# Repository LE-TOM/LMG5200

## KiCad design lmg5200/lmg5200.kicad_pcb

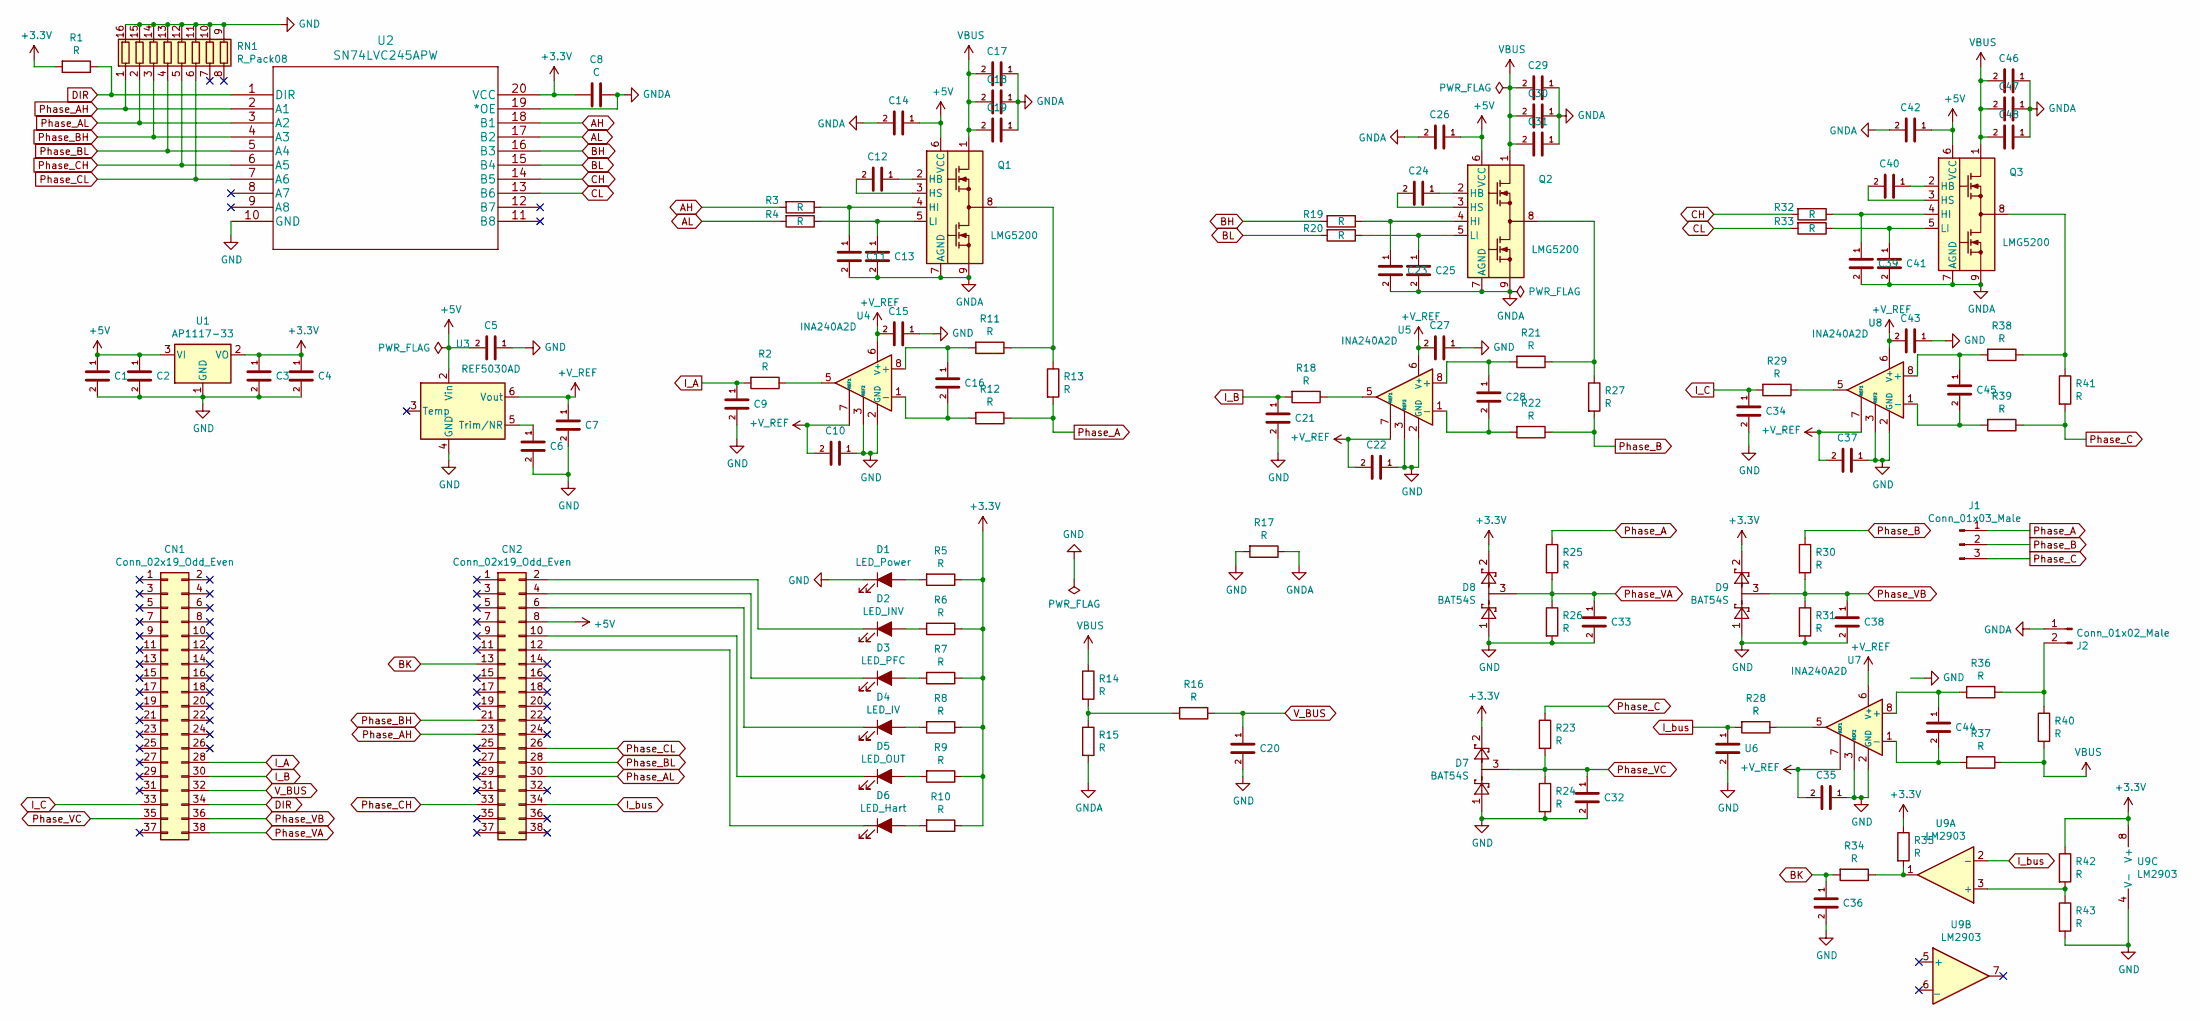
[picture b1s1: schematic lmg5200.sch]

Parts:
C1, C2, C3, C4, C5, C6, C7, C9, C10, C11, C12, C13, C14, C15, C16, C20, C21, C22, C23, C24, C25, C26, C27, C28, C32, C33, C34, C35, C36, C37, C38, C39, C40, C41, C42, C43, C44, C45: CAP; C_0805_2012Metric
C8: C; C_0805_2012Metric
C17, C18, C19, C29, C30, C31, C46, C47, C48: CAP; C_1206_3216Metric
CN1, CN2: Conn_02x19_Odd_Even; PinHeader_2x23_P2.54mm_Vertical
D1: LED_Power; LED_0805_2012Metric
D2: LED_INV; LED_0805_2012Metric
D3: LED_PFC; LED_0805_2012Metric
D4: LED_IV; LED_0805_2012Metric
D5: LED_OUT; LED_0805_2012Metric
D6: LED_Hart; LED_0805_2012Metric
D7, D8, D9: BAT54S; SOT-23
J1: Conn_01x03_Male; PhoenixContact_MSTB_2,5_3-GF_1x03_P5.00mm_Horizontal_Thread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
J2: Conn_01x02_Male; PhoenixContact_MSTB_2,5_2-GF_1x02_P5.00mm_Horizontal_Thread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
Q1, Q2, Q3: LMG5200; Texas_MOF0009A
R1, R2, R3, R4, R5, R6, R7, R8, R9, R10, R11, R12, R14, R15, R16, R17, R18, R19, R20, R21, R22, R23, R24, R25, R26, R28, R29, R30, R31, R32, R33, R34, R35, R36, R37, R38, R39, R42, R43: R; R_0805_2012Metric
R13, R27, R40, R41: R; R_2512_6332Metric
RN1: R_Pack08; R_Array_Convex_8x0602
U1: AP1117-33; SOT-223-3_TabPin2
U2: SN74LVC245APW; SOIC-20W_7.5x12.8mm_P1.27mm
U3: REF5030AD; SOIC-8_3.9x4.9mm_P1.27mm
U4, U5, U7, U8: INA240A2D; SOIC-8_3.9x4.9mm_P1.27mm
U6: CAP; C_0805_2012Metric
U9: LM2903; SOIC-8-N7_3.9x4.9mm_P1.27mm

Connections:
+5V: C1.1, C2.1, C5.2, C14.1, C26.1, C42.1, CN2.8, Q1.6 (VCC), Q2.6 (VCC), Q3.6 (VCC), U1.3 (VI), U3.2 (Vin)
AH: R3.2, U2.18 (B1)
AL: R4.2, U2.17 (B2)
BH: R19.2, U2.16 (B3)
BK: C36.1, CN2.13, R34.2
BL: R20.2, U2.15 (B4)
CH: R32.2, U2.14 (B5)
CL: R33.2, U2.13 (B6)
DIR: CN1.34, R1.1, U2.1 (DIR)
GND: C1.2, C2.2, C3.2, C4.2, C5.1, C6.2, C7.2, C9.2, C10.1, C15.1, C20.2, C21.2, C22.1, C27.1, C32.2, C33.2, C34.2, C35.1, C36.2, C37.1, C38.2, C43.1, D1.1 (K), D7.1, D8.1, D9.1, R17.2, R24.2, R26.2, R31.2, R43.2, RN1.9 (R8.2), RN1.10 (R7.2), RN1.11 (R6.2), RN1.12 (R5.2), RN1.13 (R4.2), RN1.14 (R3.2), RN1.15 (R2.2), RN1.16 (R1.2), U1.1 (GND), U2.10 (GND), U3.4 (GND), U4.2 (GND), U4.3 (REF2), U4.4 (GND), U5.2 (GND), U5.3 (REF2), U5.4 (GND), U6.2, U7.2 (GND), U7.3 (REF2), U7.4 (GND), U8.2 (GND), U8.3 (REF2), U8.4 (GND), U9.4 (V-)
GNDA: C8.1, C11.2, C13.2, C14.2, C17.1, C18.1, C19.1, C23.2, C25.2, C26.2, C29.1, C30.1, C31.1, C39.2, C41.2, C42.2, C46.1, C47.1, C48.1, J2.1, Q1.7 (AGND), Q1.9, Q2.7 (AGND), Q2.9, Q3.7 (AGND), Q3.9, R15.2, R17.1, U2.19 (*OE)
I_A: C9.1, CN1.28, R2.2
I_B: C21.1, CN1.30, R18.2
I_C: C34.1, CN1.33, R29.2
I_bus: CN2.34, R28.2, U6.1, U9.2 (-)
unnamed: C6.1, U3.5 (Trim/NR)
unnamed: C11.1, Q1.4 (HI), R3.1
unnamed: C12.1, Q1.2 (HB)
unnamed: C12.2, Q1.3 (HS)
unnamed: C13.1, Q1.5 (LI), R4.1
unnamed: C16.1, R11.2, U4.8 (+)
unnamed: C16.2, R12.2, U4.1 (-)
unnamed: C23.1, Q2.4 (HI), R19.1
unnamed: C24.1, Q2.2 (HB)
unnamed: C24.2, Q2.3 (HS)
unnamed: C25.1, Q2.5 (LI), R20.1
unnamed: C28.1, R21.2, U5.8 (+)
unnamed: C28.2, R22.2, U5.1 (-)
unnamed: C39.1, Q3.4 (HI), R32.1
unnamed: C40.1, Q3.2 (HB)
unnamed: C40.2, Q3.3 (HS)
unnamed: C41.1, Q3.5 (LI), R33.1
unnamed: C44.1, R36.2, U7.8 (+)
unnamed: C44.2, R37.2, U7.1 (-)
unnamed: C45.1, R38.2, U8.8 (+)
unnamed: C45.2, R39.2, U8.1 (-)
unnamed: CN2.2, D2.1 (K)
unnamed: CN2.4, D3.1 (K)
unnamed: CN2.6, D4.1 (K)
unnamed: CN2.10, D5.1 (K)
unnamed: CN2.12, D6.1 (K)
unnamed: D1.2 (A), R5.2
unnamed: D2.2 (A), R6.2
unnamed: D3.2 (A), R7.2
unnamed: D4.2 (A), R8.2
unnamed: D5.2 (A), R9.2
unnamed: D6.2 (A), R10.2
unnamed: J2.2, R36.1, R40.1
unnamed: Q1.8, R11.1, R13.1
unnamed: Q2.8, R21.1, R27.1
unnamed: Q3.8, R38.1, R41.1
unnamed: R2.1, U4.5
unnamed: R14.2, R15.1, R16.2
unnamed: R18.1, U5.5
unnamed: R28.1, U7.5
unnamed: R29.1, U8.5
unnamed: R34.1, R35.2, U9.1
unnamed: R42.2, R43.1, U9.3 (+)
Phase_A: J1.1, R12.1, R13.2, R25.1
Phase_AH: CN2.23, RN1.1 (R1.1), U2.2 (A1)
Phase_AL: CN2.30, RN1.2 (R2.1), U2.3 (A2)
Phase_B: J1.2, R22.1, R27.2, R30.1
Phase_BH: CN2.21, RN1.3 (R3.1), U2.4 (A3)
Phase_BL: CN2.28, RN1.4 (R4.1), U2.5 (A4)
Phase_C: J1.3, R23.1, R39.1, R41.2
Phase_CH: CN2.33, RN1.5 (R5.1), U2.6 (A5)
Phase_CL: CN2.26, RN1.6 (R6.1), U2.7 (A6)
Phase_VA: C33.1, CN1.38, D8.3, R25.2, R26.1
Phase_VB: C38.1, CN1.36, D9.3, R30.2, R31.1
Phase_VC: C32.1, CN1.35, D7.3, R23.2, R24.1
VBUS: C17.2, C18.2, C19.2, C29.2, C30.2, C31.2, C46.2, C47.2, C48.2, Q1.1, Q2.1, Q3.1, R14.1, R37.1, R40.2
V_BUS: C20.1, CN1.32, R16.1

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
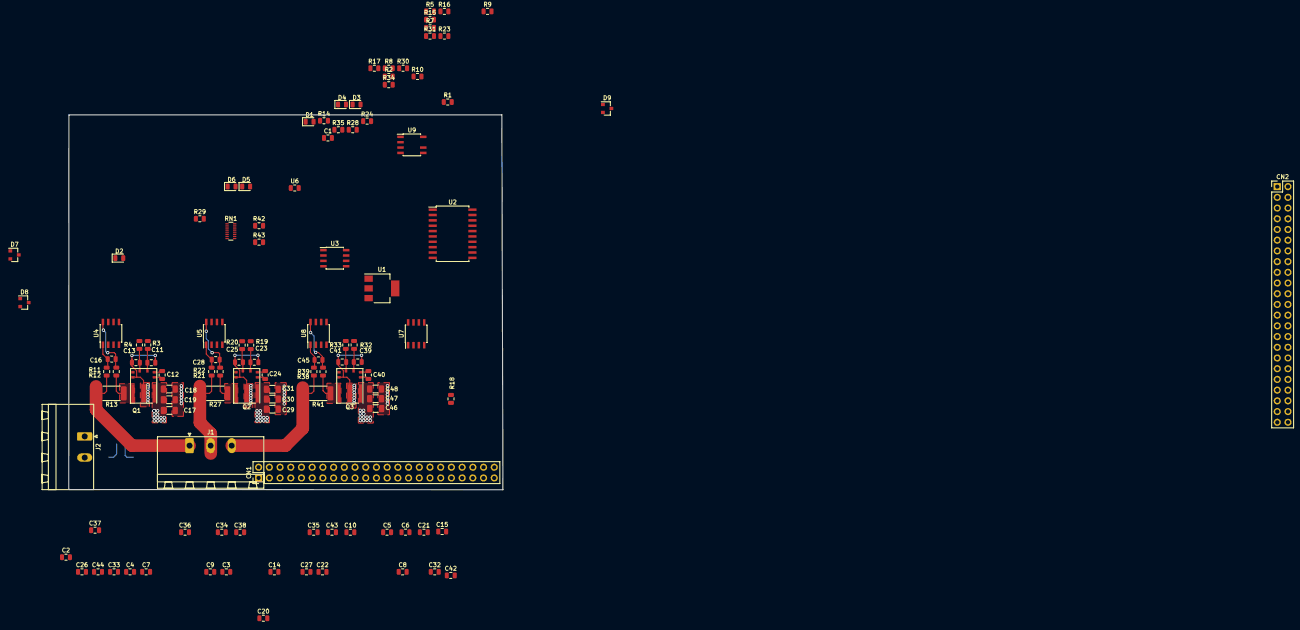
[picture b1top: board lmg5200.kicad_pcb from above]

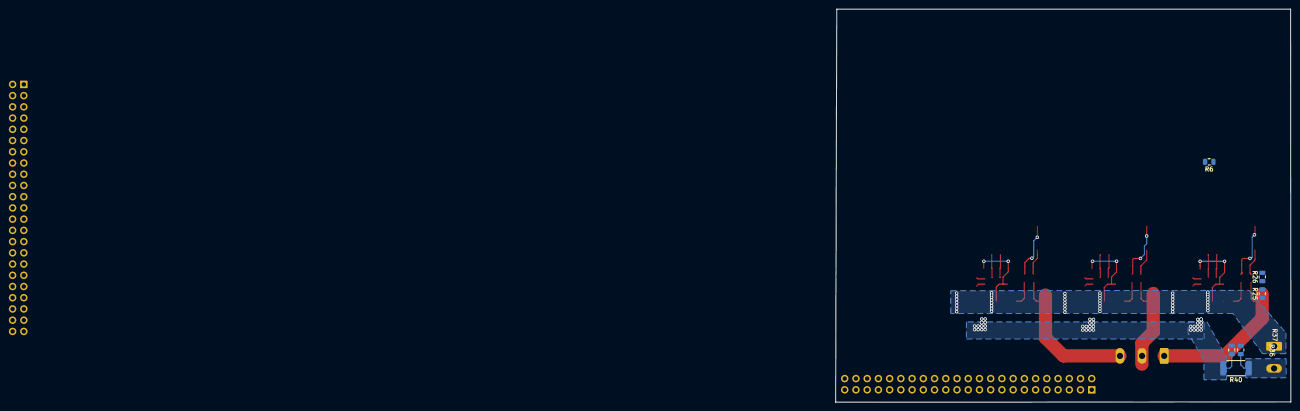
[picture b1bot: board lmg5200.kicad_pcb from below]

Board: 2 copper layers, 103.0 x 88.9 mm, 117 parts (6 on the bottom side), 73 nets.

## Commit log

2019-08-19 lmg5200 test svpwm pfc
